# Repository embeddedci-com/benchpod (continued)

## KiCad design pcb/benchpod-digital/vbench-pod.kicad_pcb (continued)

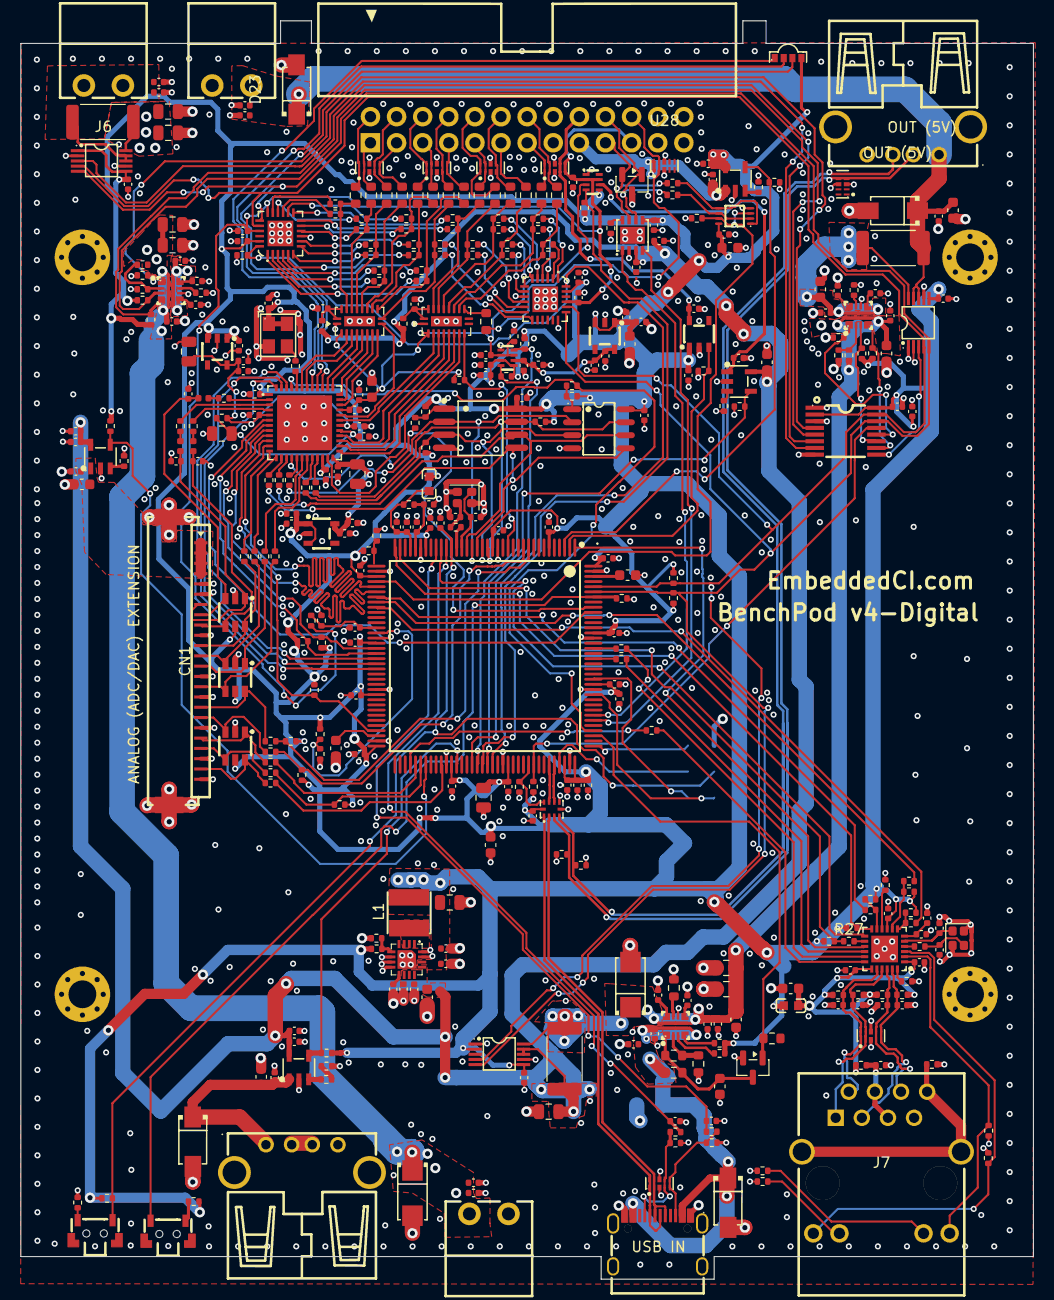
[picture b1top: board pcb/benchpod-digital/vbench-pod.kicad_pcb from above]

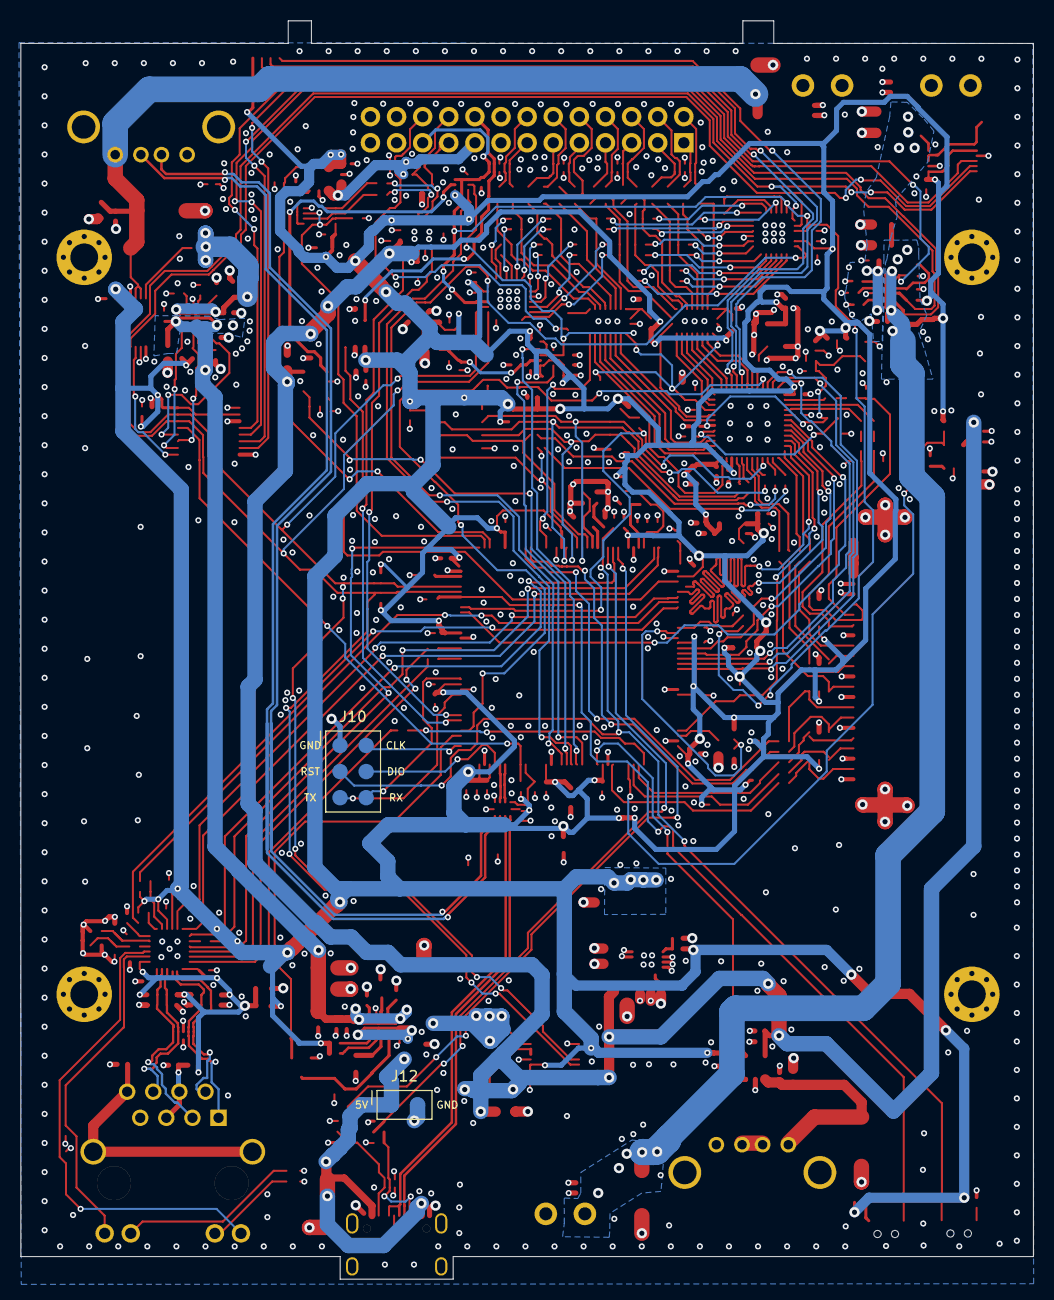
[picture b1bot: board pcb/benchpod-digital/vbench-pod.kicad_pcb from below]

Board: 4 copper layers, 98.5 x 122.4 mm, 393 parts (2 on the bottom side), 267 nets.

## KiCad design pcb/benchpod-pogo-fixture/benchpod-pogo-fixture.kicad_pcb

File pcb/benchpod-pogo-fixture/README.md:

# BenchPod v4 pogo fixture

A passive fixture for flashing and testing BenchPod v4 digital boards. Eight SMD pogo pins touch two
groups of test pads on the bottom of the pod:

- **J10** (6 pads, right of the STM32): SWD, NRST and the USART2 console.
- **J12** (2 pads, next to the input eFuse U57): 5 V and GND.

The fixture board lies flat in a printed stand with a toggle clamp lever (benchpod-private,
`enclosure/pogo_fixture_stand.py`). Per pod: drop it on the four pins, push the lever down, flash,
lift the lever.

The board is drawn in the same coordinates as `../benchpod-digital/vbench-pod.kicad_pcb`, so every
hole and pin lines up with the pod.

## Parts

| Ref | Part | Notes |
|---|---|---|
| P1–P8 | BAT WIRELESS BWCD-L6.5W2.0H2.0, LCSC C2826552 | SMD pogo pin, 6.5 mm, 2.0 mm plunger out, 100 g; JLC reflows them. In the BOM and placement files. |
| J1 | 1×8 right-angle pin header, 2.54 mm | Goes to the controller pod; the pins hang over the bottom edge |
| H1, H2 | 6.4 mm holes | The stand's posts under the pod's H11/H14 come up through them |
| H3, H4 | M2.5 plated holes | M2.5×8 screws into the stand's floor |

The stand holds the pod 5.5 mm above the fixture board, which presses the pins 1.0 mm.

## Pin map

| Pin | Pod pad | Net | J1 |
|---|---|---|---|
| P1 | J10.1 | GND | 5 |
| P2 | J10.2 | SWCLK | 4 |
| P3 | J10.3 | NRST | 6 |
| P4 | J10.4 | SWDIO | 3 |
| P5 | J10.5 | USART2_TX (the pod's console out) | 7 |
| P6 | J10.6 | USART2_RX | 2 |
| P7 | J12.1 | +5V_EFUSE (before the pod's input eFuse) | 8 |
| P8 | J12.2 | GND | 5 |

J1: 1 GND, 2 POD_RX, 3 SWDIO, 4 SWCLK, 5 GND, 6 NRST, 7 POD_TX, 8 POD_5V.

## Using it

Wire J1 to a controller BenchPod. Use its target power for POD_5V, three LA channels for SWDIO,
SWCLK and NRST, and a UART receive channel on POD_TX. A loop on the controller then:

1. Keeps target power on, current-limited, and waits until the pod draws current.
2. Waits for the boot banner on the UART.
3. Flashes the pod over SWD.
4. Reads the self-test result and shows pass or fail.
5. Waits for the current to drop when the pod comes off.

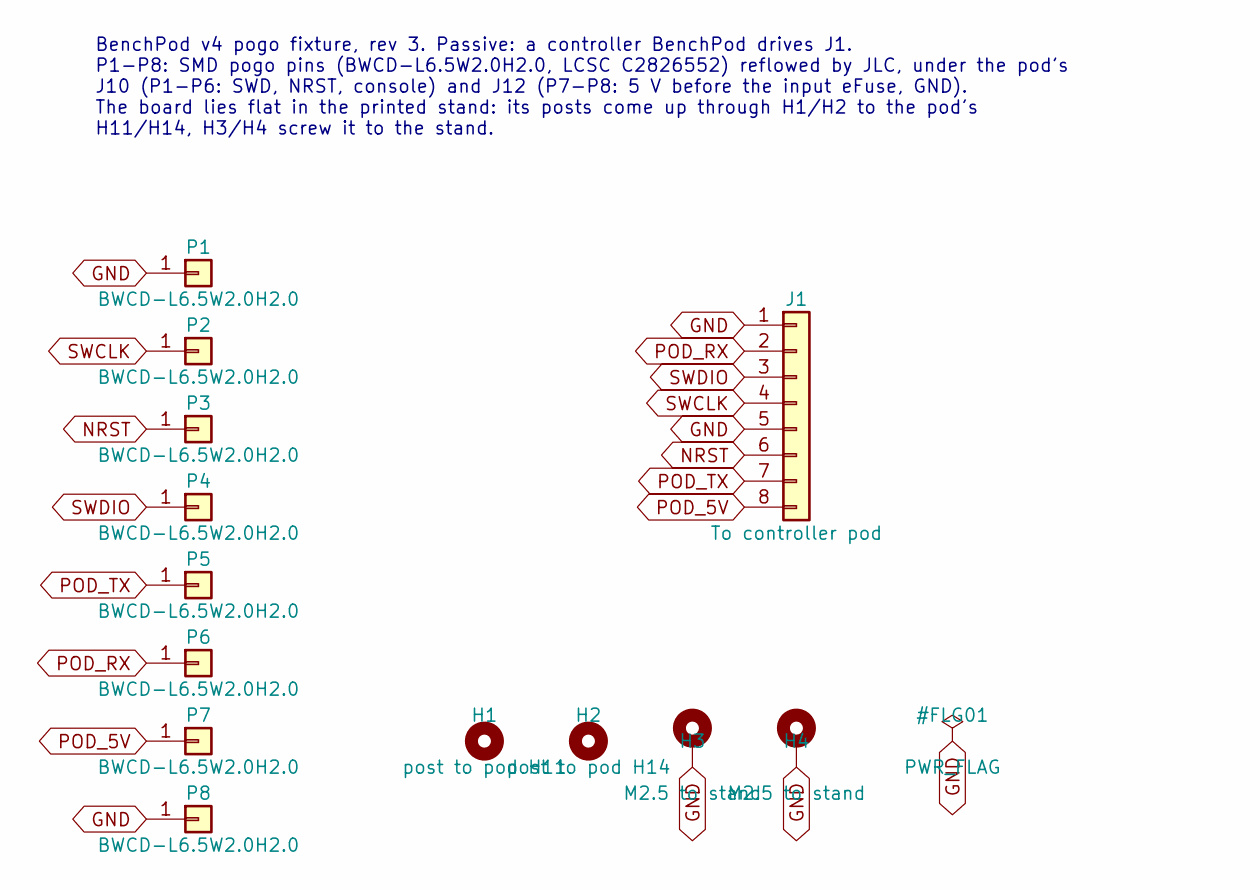
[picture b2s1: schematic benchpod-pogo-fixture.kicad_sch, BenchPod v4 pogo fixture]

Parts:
H1: post to pod H11; MountingHole_6.4mm_M6
H2: post to pod H14; MountingHole_6.4mm_M6
H3, H4: M2.5 to stand; MountingHole_2.7mm_M2.5_Pad_Via
J1: To controller pod; PinHeader_1x08_P2.54mm_Horizontal
P1, P2, P3, P4, P5, P6, P7, P8: BWCD-L6.5W2.0H2.0; Pogo_SMD_BWCD-L6.5W2.0H2.0; LCSC C2826552

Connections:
GND: H3.1, H4.1, J1.1, J1.5, P1.1, P8.1
NRST: J1.6, P3.1
POD_5V: J1.8, P7.1
POD_RX: J1.2, P6.1
POD_TX: J1.7, P5.1
SWCLK: J1.4, P2.1
SWDIO: J1.3, P4.1

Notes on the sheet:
BenchPod v4 pogo fixture, rev 3. Passive: a controller BenchPod drives J1. P1-P8: SMD pogo pins (BWCD-L6.5W2.0H2.0, LCSC C2826552) reflowed by JLC, under the pod's J10 (P1-P6: SWD, NRST, console) and J12 (P7-P8: 5 V before the input eFuse, GND). The board lies flat in the printed stand: its posts c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

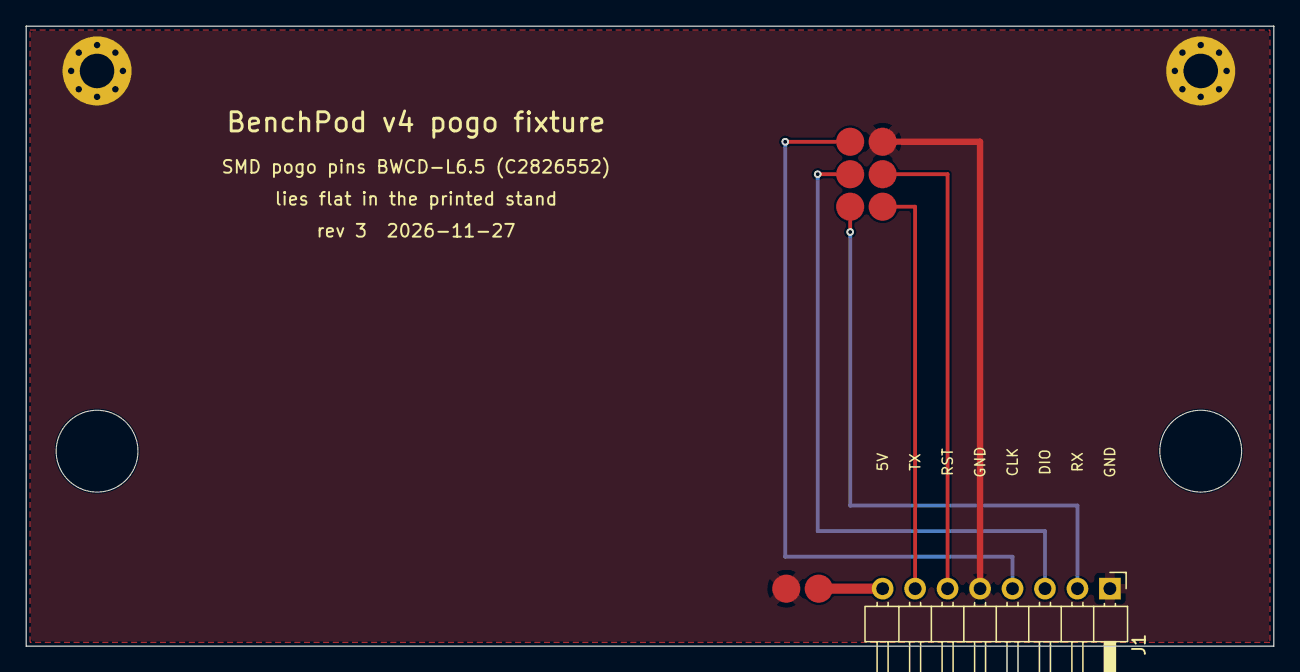
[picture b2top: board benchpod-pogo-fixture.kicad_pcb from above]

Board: 2 copper layers, 97.6 x 48.5 mm, 13 parts (0 on the bottom side), 7 nets.

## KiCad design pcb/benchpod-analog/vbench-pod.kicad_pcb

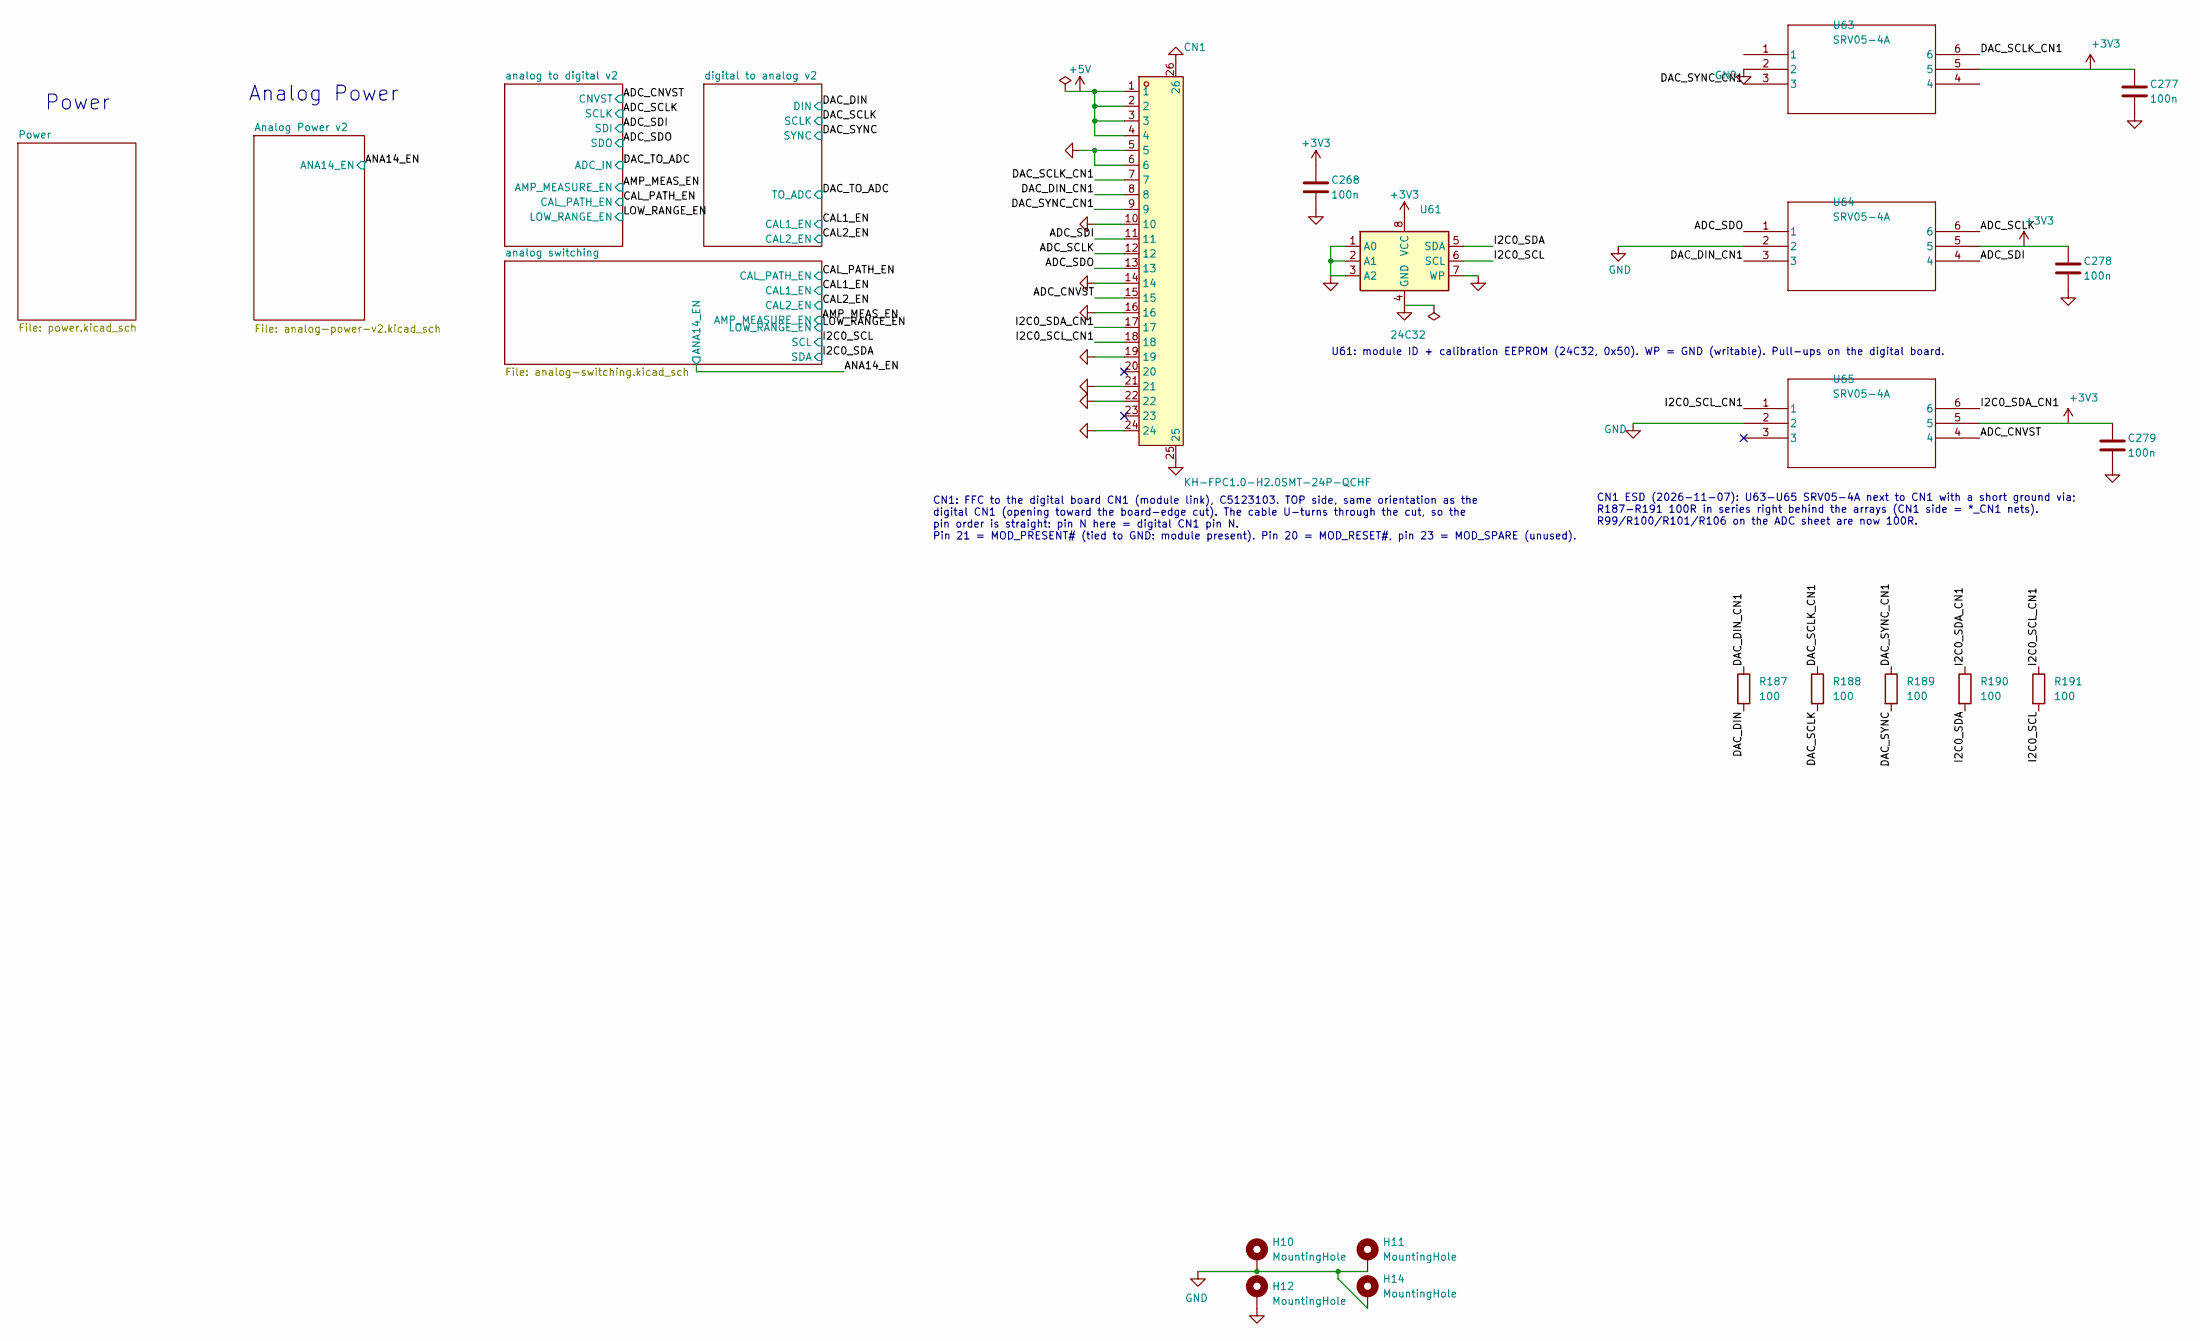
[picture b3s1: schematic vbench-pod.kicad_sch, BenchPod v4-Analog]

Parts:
C268, C277, C278, C279: 100n; C_0402_1005Metric; LCSC C307331
CN1: KH-FPC1.0-H2.0SMT-24P-QCHF; C5123103_FPC-SMD_24P-P1.00_KH-FPC1.0-H2.0SMT-24P-QCHF; LCSC C5123103
H10, H11, H12, H14: MountingHole; MountingHole_2.7mm_M2.5_Pad_Via
R187, R188, R189, R190, R191: 100; R_0402_1005Metric; LCSC C25076
U61: 24C32; C18723546_SOP-8_L4.9-W3.9-P1.27-LS6.0-BL; LCSC C18723546
U63, U64, U65: SRV05-4A; SOT-23-6_L2.9-W1.6-P0.95-LS2.8-BR; LCSC C20615829

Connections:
+3V3: C268.1, C277.1, C278.1, C279.1, U61.8 (VCC), U63.5, U64.5, U65.5; also elsewhere on the board
+5V: CN1.1, CN1.2, CN1.3, CN1.4; also elsewhere on the board
/ADC_CNVST: CN1.15, U65.4; also elsewhere on the board
/ADC_SCLK: CN1.12, U64.6; also elsewhere on the board
/ADC_SDI: CN1.11, U64.4; also elsewhere on the board
/ADC_SDO: CN1.13, U64.1; also elsewhere on the board
/DAC_DIN: R187.2; also elsewhere on the board
/DAC_DIN_CN1: CN1.8, R187.1, U64.3
/DAC_SCLK: R188.2; also elsewhere on the board
/DAC_SCLK_CN1: CN1.7, R188.1, U63.6
/DAC_SYNC: R189.2; also elsewhere on the board
/DAC_SYNC_CN1: CN1.9, R189.1, U63.3
/I2C0_SCL: R191.2, U61.6 (SCL); also elsewhere on the board
/I2C0_SCL_CN1: CN1.18, R191.1, U65.1
/I2C0_SDA: R190.2, U61.5 (SDA); also elsewhere on the board
/I2C0_SDA_CN1: CN1.17, R190.1, U65.6
GND: C268.2, C277.2, C278.2, C279.2, CN1.5, CN1.6, CN1.10, CN1.14, CN1.16, CN1.19, CN1.21, CN1.22, CN1.24, CN1.25, CN1.26, H10.1 (1_1), H11.1 (1_1), H12.1 (1_1), H14.1 (1_1), U61.1 (A0), U61.2 (A1), U61.3 (A2), U61.4 (GND), U61.7 (WP), U63.2, U64.2, U65.2; also elsewhere on the board

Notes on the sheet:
Analog Power
CN1: FFC to the digital board CN1 (module link), C5123103. TOP side, same orientation as the digital CN1 (opening toward the board-edge cut). The cable U-turns through the cut, so the pin order is straight: pin N here = digital CN1 pin N. Pin 21 = MOD_PRESENT# (tied to GND: module present). Pin 20 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
U61: module ID + calibration EEPROM (24C32, 0x50). WP = GND (writable). Pull-ups on the digital board.
Power
CN1 ESD (2026-11-07): U63-U65 SRV05-4A next to CN1 with a short ground via; R187-R191 100R in series right behind the arrays (CN1 side = *_CN1 nets). R99/R100/R101/R106 on the ADC sheet are now 100R.

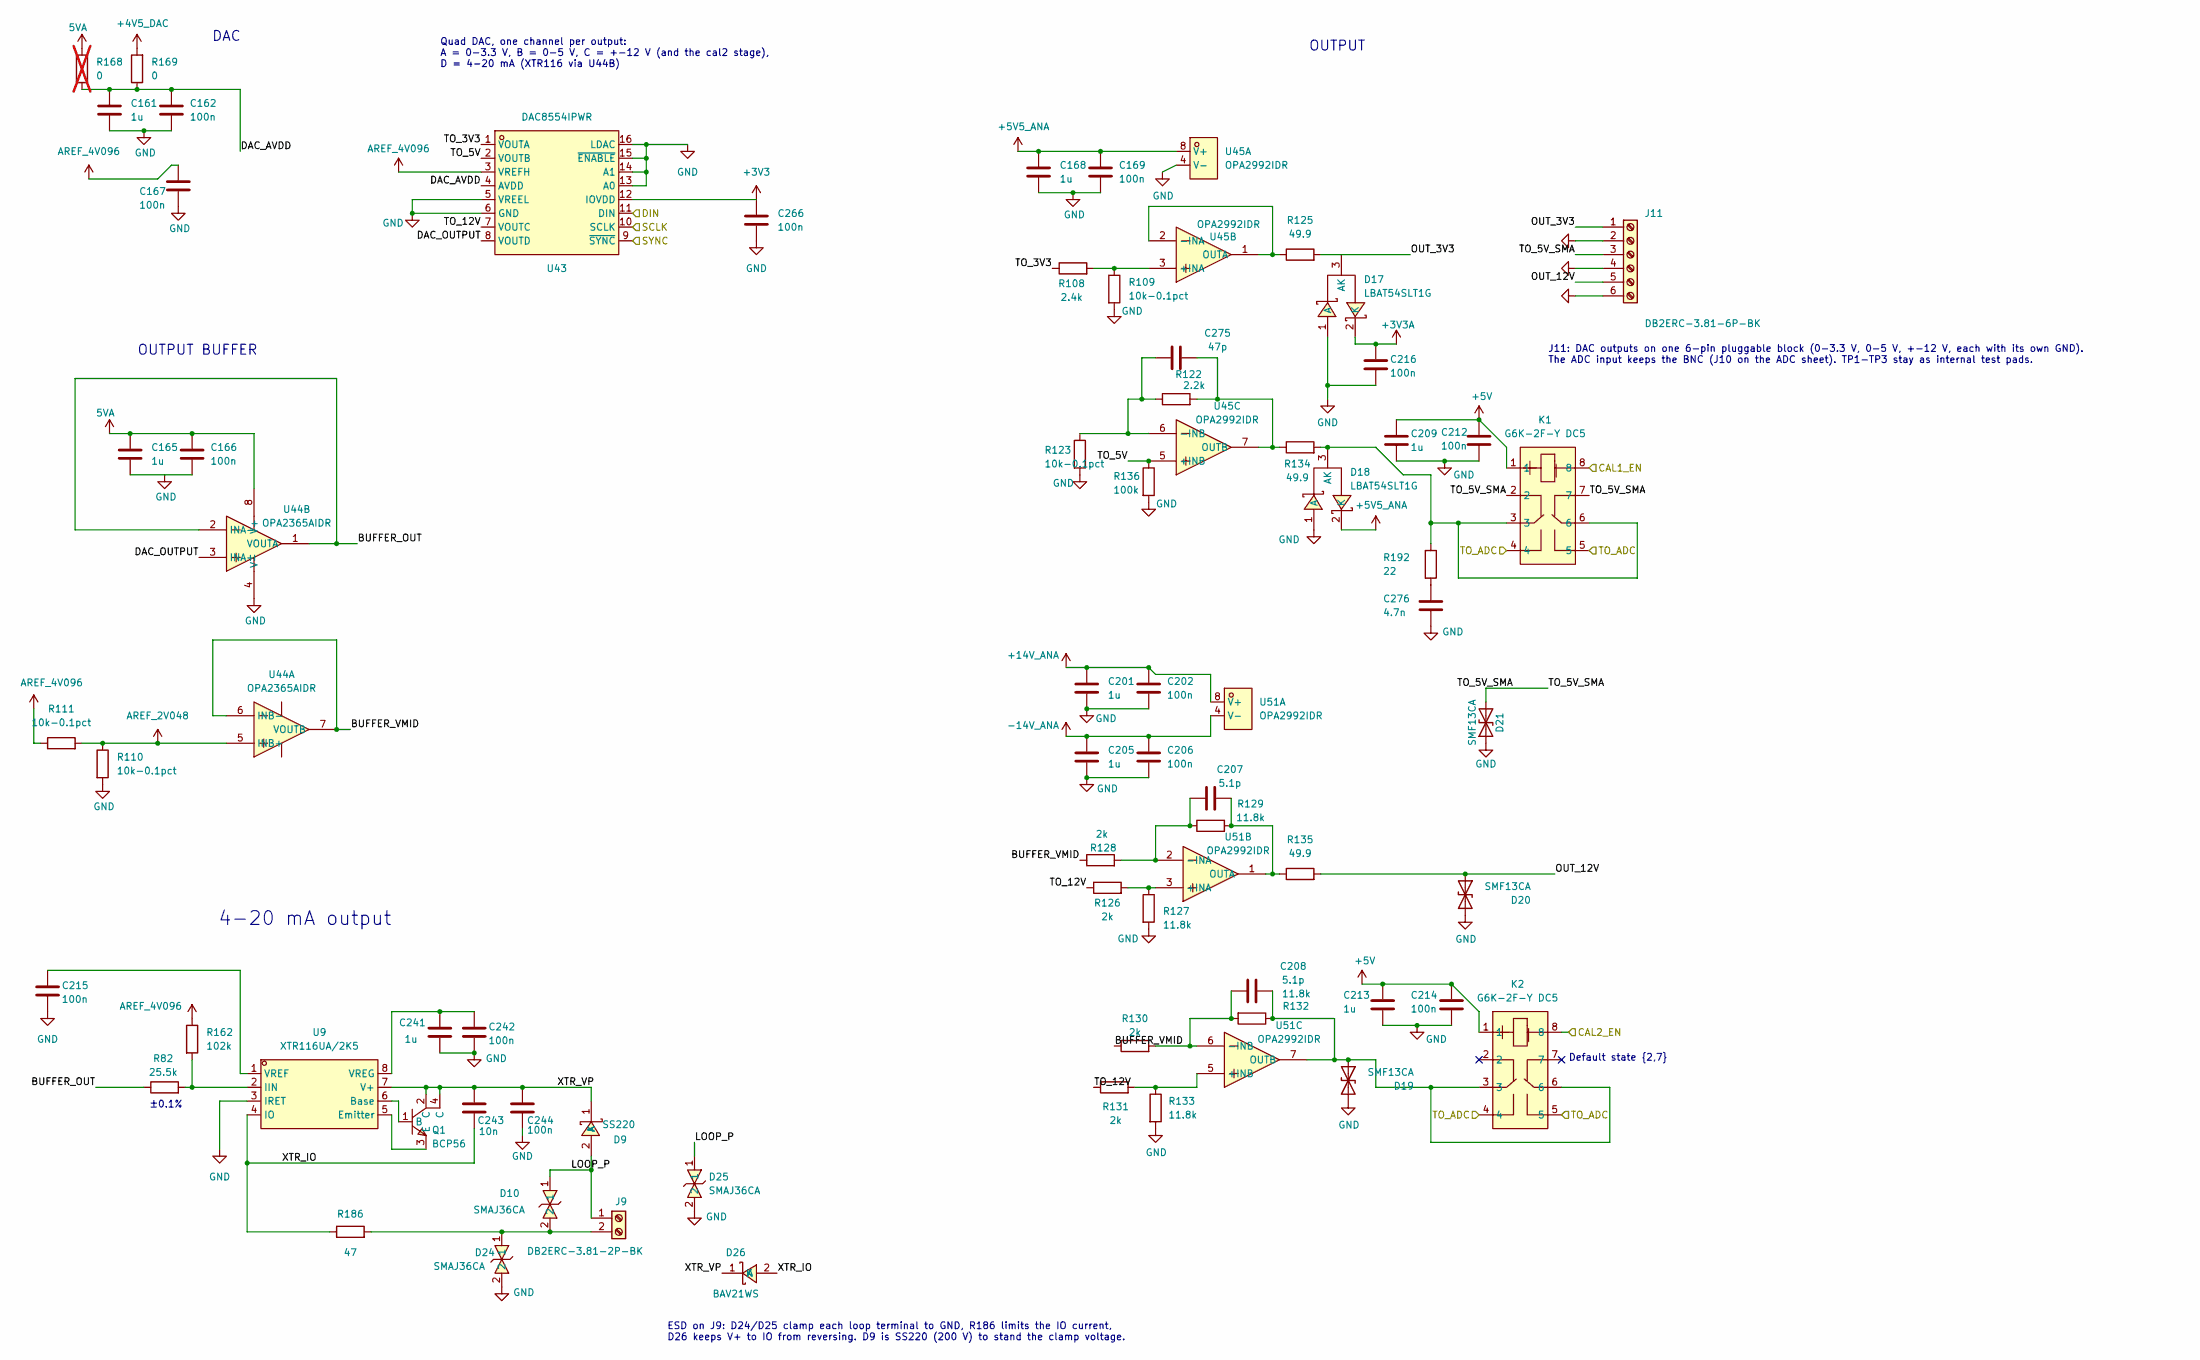
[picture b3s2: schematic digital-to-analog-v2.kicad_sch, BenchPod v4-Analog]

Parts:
C161, C201, C205, C241: 1u; C_0402_1005Metric; MPN GRM155R61H105KE05D; LCSC C1518208
C162, C166, C167, C169, C202, C206, C212, C214, C215, C216, C242, C244: 100n; C_0402_1005Metric; MPN CC0603KRX7R9BB104; LCSC C307331
C165, C168, C209, C213: 1u; C_0402_1005Metric; MPN CL05A105KA5NQNC; LCSC C52923
C207, C208: 5.1p; C_0603_1608Metric; LCSC C20617868
C243: 10n; C_0402_1005Metric; LCSC C15195
C266: 100n; C_0402_1005Metric; LCSC C307331
C275: 47p; C_0402_1005Metric; LCSC C1567
C276: 4.7n; C_0603_1608Metric; LCSC C85980
D9: SS220; SMA_L4.3-W2.6-LS5.2-RD; MPN SS220; LCSC Part C7420361
D10, D24, D25: SMAJ36CA; SMA_L4.3-W2.6-LS5.0-BI; MPN SMAJ36CA; LCSC Part C5353135
D17, D18: LBAT54SLT1G; SOT-23_L2.9-W1.3-P1.90-LS2.4-BR; MPN LBAT54SLT1G; LCSC Part C12765
D19, D20: SMF13CA; SOD-123FL_L3.0-W1.8-LS3.7-BI; MPN SMF13CA; LCSC Part C1851355
D21: SMF13CA; SOD-123FL_L3.0-W1.8-LS3.7-BI; MPN SMF13CA; LCSC C1851355
D26: BAV21WS; D_SOD-323; MPN BAV21WS; LCSC Part C7420334
J9: DB2ERC-3.81-2P-BK; C5259145_CONN-TH_2P-P3.81_DB2ERC-3.81-2P-BK; MFR. Part # DB2ERC-3.81-2P-BK; LCSC Part # C5259145
J11: DB2ERC-3.81-6P-BK; C5244107_HDR-TH_DB2ERC-3.81-6P-BK; LCSC C5244107
K1, K2: G6K-2F-Y DC5; RELAY-TH_G6K-2F-Y; MPN G6K-2F-Y-TR DC5 BY OMR/C; LCSC Part C231390
Q1: BCP56; SOT-223-4_L6.5-W3.5-P2.30-LS7.0-BR; MPN BCP56; LCSC C5345976
R82: 25.5k; R_0603_1608Metric; LCSC C861257
R108: 2.4k; R_0603_1608Metric; LCSC C861300
R109, R110, R111, R123: 10k-0.1pct; R_0402_1005Metric; LCSC C190095
R122: 2.2k; R_0402_1005Metric; LCSC C326602
R125, R134, R135: 49.9; R_0805_2012Metric; LCSC C77379
R126, R128, R130, R131: 2k; R_0402_1005Metric; LCSC C852711
R127, R129, R132, R133: 11.8k; R_0402_1005Metric; LCSC C2693079
R136: 100k; R_0402_1005Metric; LCSC C25741
R162: 102k; R_0603_1608Metric; LCSC C861068
R168: 0; R_0402_1005Metric; LCSC C17168; not fitted
R169: 0; R_0402_1005Metric; LCSC C17168
R186: 47; R_0603_1608Metric; LCSC C23182
R192: 22; R_0603_1608Metric; LCSC C23345
U9: XTR116UA/2K5; SOIC-8_L5.0-W4.0-P1.27-LS6.0-BL; MPN XTR116UA/2K5; LCSC Part C368611
U43: DAC8554IPWR; C527522_TSSOP-16_L5_0-W4_4-P0_65-LS6_4-BL; MPN DAC8554IPWR; LCSC C527522
U44: OPA2365AIDR; SOIC-8_L4.9-W3.9-P1.27-LS6.0-BL; MPN OPA2365AIDR; LCSC Part C130011
U45, U51: OPA2992IDR; SOIC-8_L4.9-W3.9-P1.27-LS6.0-BL; MPN OPA2992IDR; LCSC Part C4368953

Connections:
5VA: C165.2, C166.2, R168.2, U44.8 (V+); also elsewhere on the board
+3V3: C266.1, U43.12 (IOVDD); also elsewhere on the board
+3V3A: C216.2, D17.2 (K); also elsewhere on the board
+4V5_DAC: R169.2; also elsewhere on the board
+5V: C209.2, C212.2, C213.2, C214.2, K1.1, K2.1; also elsewhere on the board
+5V5_ANA: C168.2, C169.2, D18.2 (K), U45.8 (V+); also elsewhere on the board
+14V_ANA: C201.2, C202.2, U51.8 (V+); also elsewhere on the board
-14V_ANA: C205.2, C206.2, U51.4 (V-); also elsewhere on the board
/CAL1_EN: K1.8; also elsewhere on the board
/CAL2_EN: K2.8; also elsewhere on the board
/DAC_DIN: U43.11 (DIN); also elsewhere on the board
/DAC_SCLK: U43.10 (SCLK); also elsewhere on the board
/DAC_SYNC: U43.9 (~SYNC); also elsewhere on the board
/DAC_TO_ADC: K1.4, K1.5, K2.4, K2.5; also elsewhere on the board
/digital to analog v2/BUFFER_OUT: R82.1, U44.1 (VOUTA), U44.2 (INA-)
/digital to analog v2/BUFFER_VMID: R128.1, R130.1, U44.6 (INB-), U44.7 (VOUTB)
/digital to analog v2/DAC_AVDD: C161.2, C162.2, R168.1, R169.1, U43.4 (AVDD)
/digital to analog v2/DAC_OUTPUT: U43.8 (VOUTD), U44.3 (INA+)
/digital to analog v2/LOOP_P: D9.2 (A), D10.1, D25.1, J9.1
/digital to analog v2/OUT_3V3: D17.3 (AK), J11.1, R125.2
/digital to analog v2/OUT_12V: D20.1 (A1), J11.5, R135.2
/digital to analog v2/TO_3V3: R108.1, U43.1 (VOUTA)
/digital to analog v2/TO_5V: R136.1, U43.2 (VOUTB), U45.5 (+INB)
/digital to analog v2/TO_5V_SMA: D21.2 (A2), J11.3, K1.2, K1.7
/digital to analog v2/TO_12V: R126.1, R131.1, U43.7 (VOUTC)
/digital to analog v2/XTR_IO: C243.2, D26.2 (A), R186.1, U9.4 (IO)
/digital to analog v2/XTR_VP: C243.1, C244.2, D9.1 (K), D26.1 (K), Q1.2 (C), Q1.4 (C), U9.7 (V+)
AREF_2V048: R110.1, R111.2, U44.5 (INB+)
AREF_4V096: C167.2, R111.1, R162.1, U43.3 (VREFH); also elsewhere on the board
GND: C161.1, C162.1, C165.1, C166.1, C167.1, C168.1, C169.1, C201.1, C202.1, C205.1, C206.1, C209.1, C212.1, C213.1, C214.1, C215.1, C216.1, C241.1, C242.1, C244.1, C266.2, C276.2, D17.1 (A), D18.1 (A), D19.2 (A2), D20.2 (A2), D21.1 (A1), D24.2, D25.2, J11.2, J11.4, J11.6, R109.2, R110.2, R123.2, R127.2, R133.2, R136.2, U9.3 (IRET), U43.5 (VREEL), U43.6 (GND), U43.13 (A0), U43.14 (A1), U43.15 (~ENABLE), U43.16 (LDAC), U44.4 (V-), U45.4 (V-); also elsewhere on the board
unnamed: C276.1, R192.2
unnamed: D18.3 (AK), K1.3, K1.6, R134.2, R192.1
unnamed: C208.2, D19.1 (A1), K2.3, K2.6, R132.1, U51.7 (OUTB)
unnamed: D10.2, D24.1, J9.2, R186.2
unnamed: Q1.1 (B), U9.6 (Base)
unnamed: Q1.3 (E), U9.5 (Emitter)
unnamed: R82.2, R162.2, U9.2 (IIN)
unnamed: C215.2, U9.1 (VREF)
unnamed: C241.2, C242.2, U9.8 (VREG)
unnamed: R108.2, R109.1, U45.3 (+INA)
unnamed: R125.1, U45.1 (OUTA), U45.2 (-INA)
unnamed: C275.1, R122.1, R123.1, U45.6 (-INB)
unnamed: C275.2, R122.2, R134.1, U45.7 (OUTB)
unnamed: R126.2, R127.1, U51.3 (+INA)
unnamed: C207.1, R128.2, R129.1, U51.2 (-INA)
unnamed: C207.2, R129.2, R135.1, U51.1 (OUTA)
unnamed: R131.2, R133.1, U51.5 (+INB)
unnamed: C208.1, R130.2, R132.2, U51.6 (-INB)

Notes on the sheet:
Default state {2,7}
J11: DAC outputs on one 6-pin pluggable block (0-3.3 V, 0-5 V, +-12 V, each with its own GND). The ADC input keeps the BNC (J10 on the ADC sheet). TP1-TP3 stay as internal test pads.
±0.1%
ESD on J9: D24/D25 clamp each loop terminal to GND, R186 limits the IO current, D26 keeps V+ to IO from reversing. D9 is SS220 (200 V) to stand the clamp voltage.
OUTPUT BUFFER
OUTPUT
Quad DAC, one channel per output: A = 0-3.3 V, B = 0-5 V, C = +-12 V (and the cal2 stage), D = 4-20 mA (XTR116 via U44B)
DAC
4-20 mA output

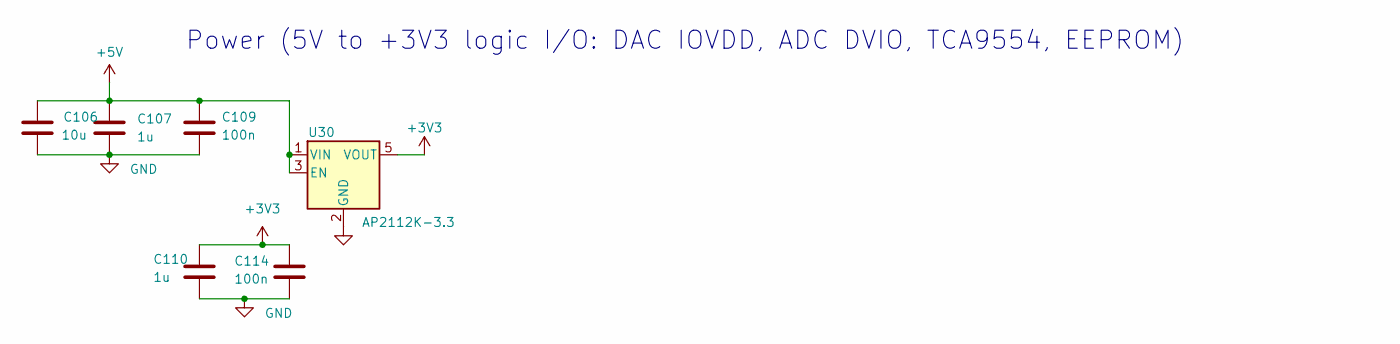
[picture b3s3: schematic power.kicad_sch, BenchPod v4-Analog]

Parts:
C106: 10u; C_0603_1608Metric; LCSC C96446
C107: 1u; C_0402_1005Metric; MPN CL05A105KA5NQNC; LCSC C52923
C109, C114: 100n; C_0402_1005Metric; MPN CC0603KRX7R9BB104; LCSC C307331
C110: 1u; C_0402_1005Metric; MPN GRM155R61H105KE05D; LCSC C1518208
U30: AP2112K-3.3; SOT-25-5_L2.9-W1.6-P0.95-LS2.8-BL; LCSC C51118

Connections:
+3V3: C110.2, C114.2, U30.5 (VOUT); also elsewhere on the board
+5V: C106.2, C107.2, C109.2, U30.1 (VIN), U30.3 (EN); also elsewhere on the board
GND: C106.1, C107.1, C109.1, C110.1, C114.1, U30.2 (GND); also elsewhere on the board

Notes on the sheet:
Power (5V to +3V3 logic I/O: DAC IOVDD, ADC DVIO, TCA9554, EEPROM)

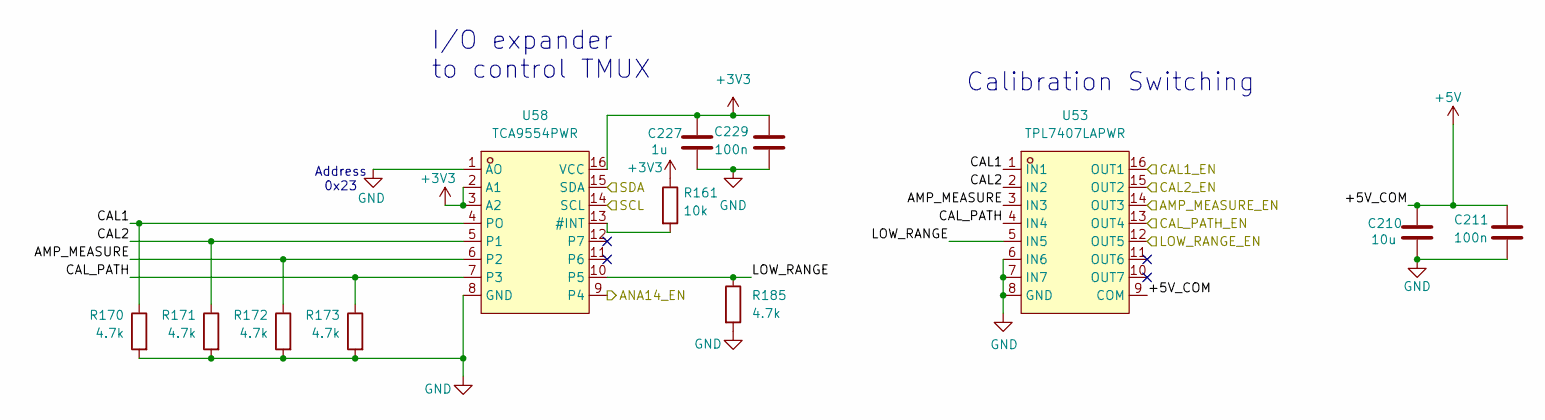
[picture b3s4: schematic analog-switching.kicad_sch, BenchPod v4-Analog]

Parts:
C210: 10u; C_0603_1608Metric; MPN CL21B105KBFNNNE; LCSC C96446
C211: 100n; C_0402_1005Metric; MPN CC0603KRX7R9BB104; LCSC C307331
C227: 1u; C_0402_1005Metric; MPN GRM155R61H105KE05D; LCSC C1518208
C229: 100n; C_0402_1005Metric; LCSC C307331
R161: 10k; R_0402_1005Metric; LCSC C25744
R170, R171, R172, R173, R185: 4.7k; R_0402_1005Metric; LCSC C25900
U53: TPL7407LAPWR; TSSOP-16_L5.0-W4.4-P0.65-LS6.4-BL; MPN TPL7407LAPWR; LCSC Part C2149827
U58: TCA9554PWR; TSSOP-16_L5.0-W4.4-P0.65-LS6.4-TL; MPN TCA9554PWR; LCSC Part C477924

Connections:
+3V3: C227.2, C229.1, R161.1, U58.2 (A1), U58.3 (A2), U58.16 (VCC); also elsewhere on the board
+5V: C210.2, C211.2, U53.9 (COM); also elsewhere on the board
/AMP_MEAS_EN: U53.14 (OUT3); also elsewhere on the board
/ANA14_EN: U58.9 (P4); also elsewhere on the board
/CAL1_EN: U53.16 (OUT1); also elsewhere on the board
/CAL2_EN: U53.15 (OUT2); also elsewhere on the board
/CAL_PATH_EN: U53.13 (OUT4); also elsewhere on the board
/I2C0_SCL: U58.14 (SCL); also elsewhere on the board
/I2C0_SDA: U58.15 (SDA); also elsewhere on the board
/LOW_RANGE_EN: U53.12 (OUT5); also elsewhere on the board
/analog switching/AMP_MEASURE: R172.1, U53.3 (IN3), U58.6 (P2)
/analog switching/CAL1: R170.1, U53.1 (IN1), U58.4 (PO)
/analog switching/CAL2: R171.1, U53.2 (IN2), U58.5 (P1)
/analog switching/CAL_PATH: R173.1, U53.4 (IN4), U58.7 (P3)
/analog switching/LOW_RANGE: R185.1, U53.5 (IN5), U58.10 (P5)
GND: C210.1, C211.1, C227.1, C229.2, R170.2, R171.2, R172.2, R173.2, R185.2, U53.6 (IN6), U53.7 (IN7), U53.8 (GND), U58.1 (AO), U58.8 (GND); also elsewhere on the board
unnamed: R161.2, U58.13 (#INT)

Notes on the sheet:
I/O expander to control TMUX
Calibration Switching
Address 0x23
